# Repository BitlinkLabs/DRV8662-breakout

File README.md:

# DRV8662-breakout

<p align="center">
  
&nbsp; &nbsp; &nbsp; &nbsp;
  
&nbsp; &nbsp; &nbsp; &nbsp;
  
</p>

### What is it?
This is a ready-to-go development board with everything necessary to run piezo actuators.
It features a DRV8662 IC from Texas Instruments and all the additional circuitry for it to work as expected.

### How does it function?
The IC serves multiple purposes. First of all it is a boost-converter to generate up 200V from the 3.3-5V it takes as an input. Secondly it features an amplifier which takes a PWM Signal and drives the Output pins to the respective differential values according to the input.

At the output you can connect a piezo actuator for haptic feedback or valves & pumps.
The output voltage is an AC Waveform with an adjustable Peak-to-Peak voltage.

### What is special about it?
The Output voltage can be to 4 approximate values: 50Vpp, 100Vpp, 150Vpp, 200Vpp using a simple dip switch.

### How do I get started?
All you need to do is connect an PWM and GND pin of a microcontroller to the PWM+ Pin and GND pin of the development board respectively. This covers the “signal” part.
To power the dev board you can either use the USB mini jack (we recommend using a USB hub for this) or through the included VCC and GND Pins. 
Be sure to stick to an input voltage of 3.3V to 5V and be aware that the USB voltage will be present on the VCC pin.

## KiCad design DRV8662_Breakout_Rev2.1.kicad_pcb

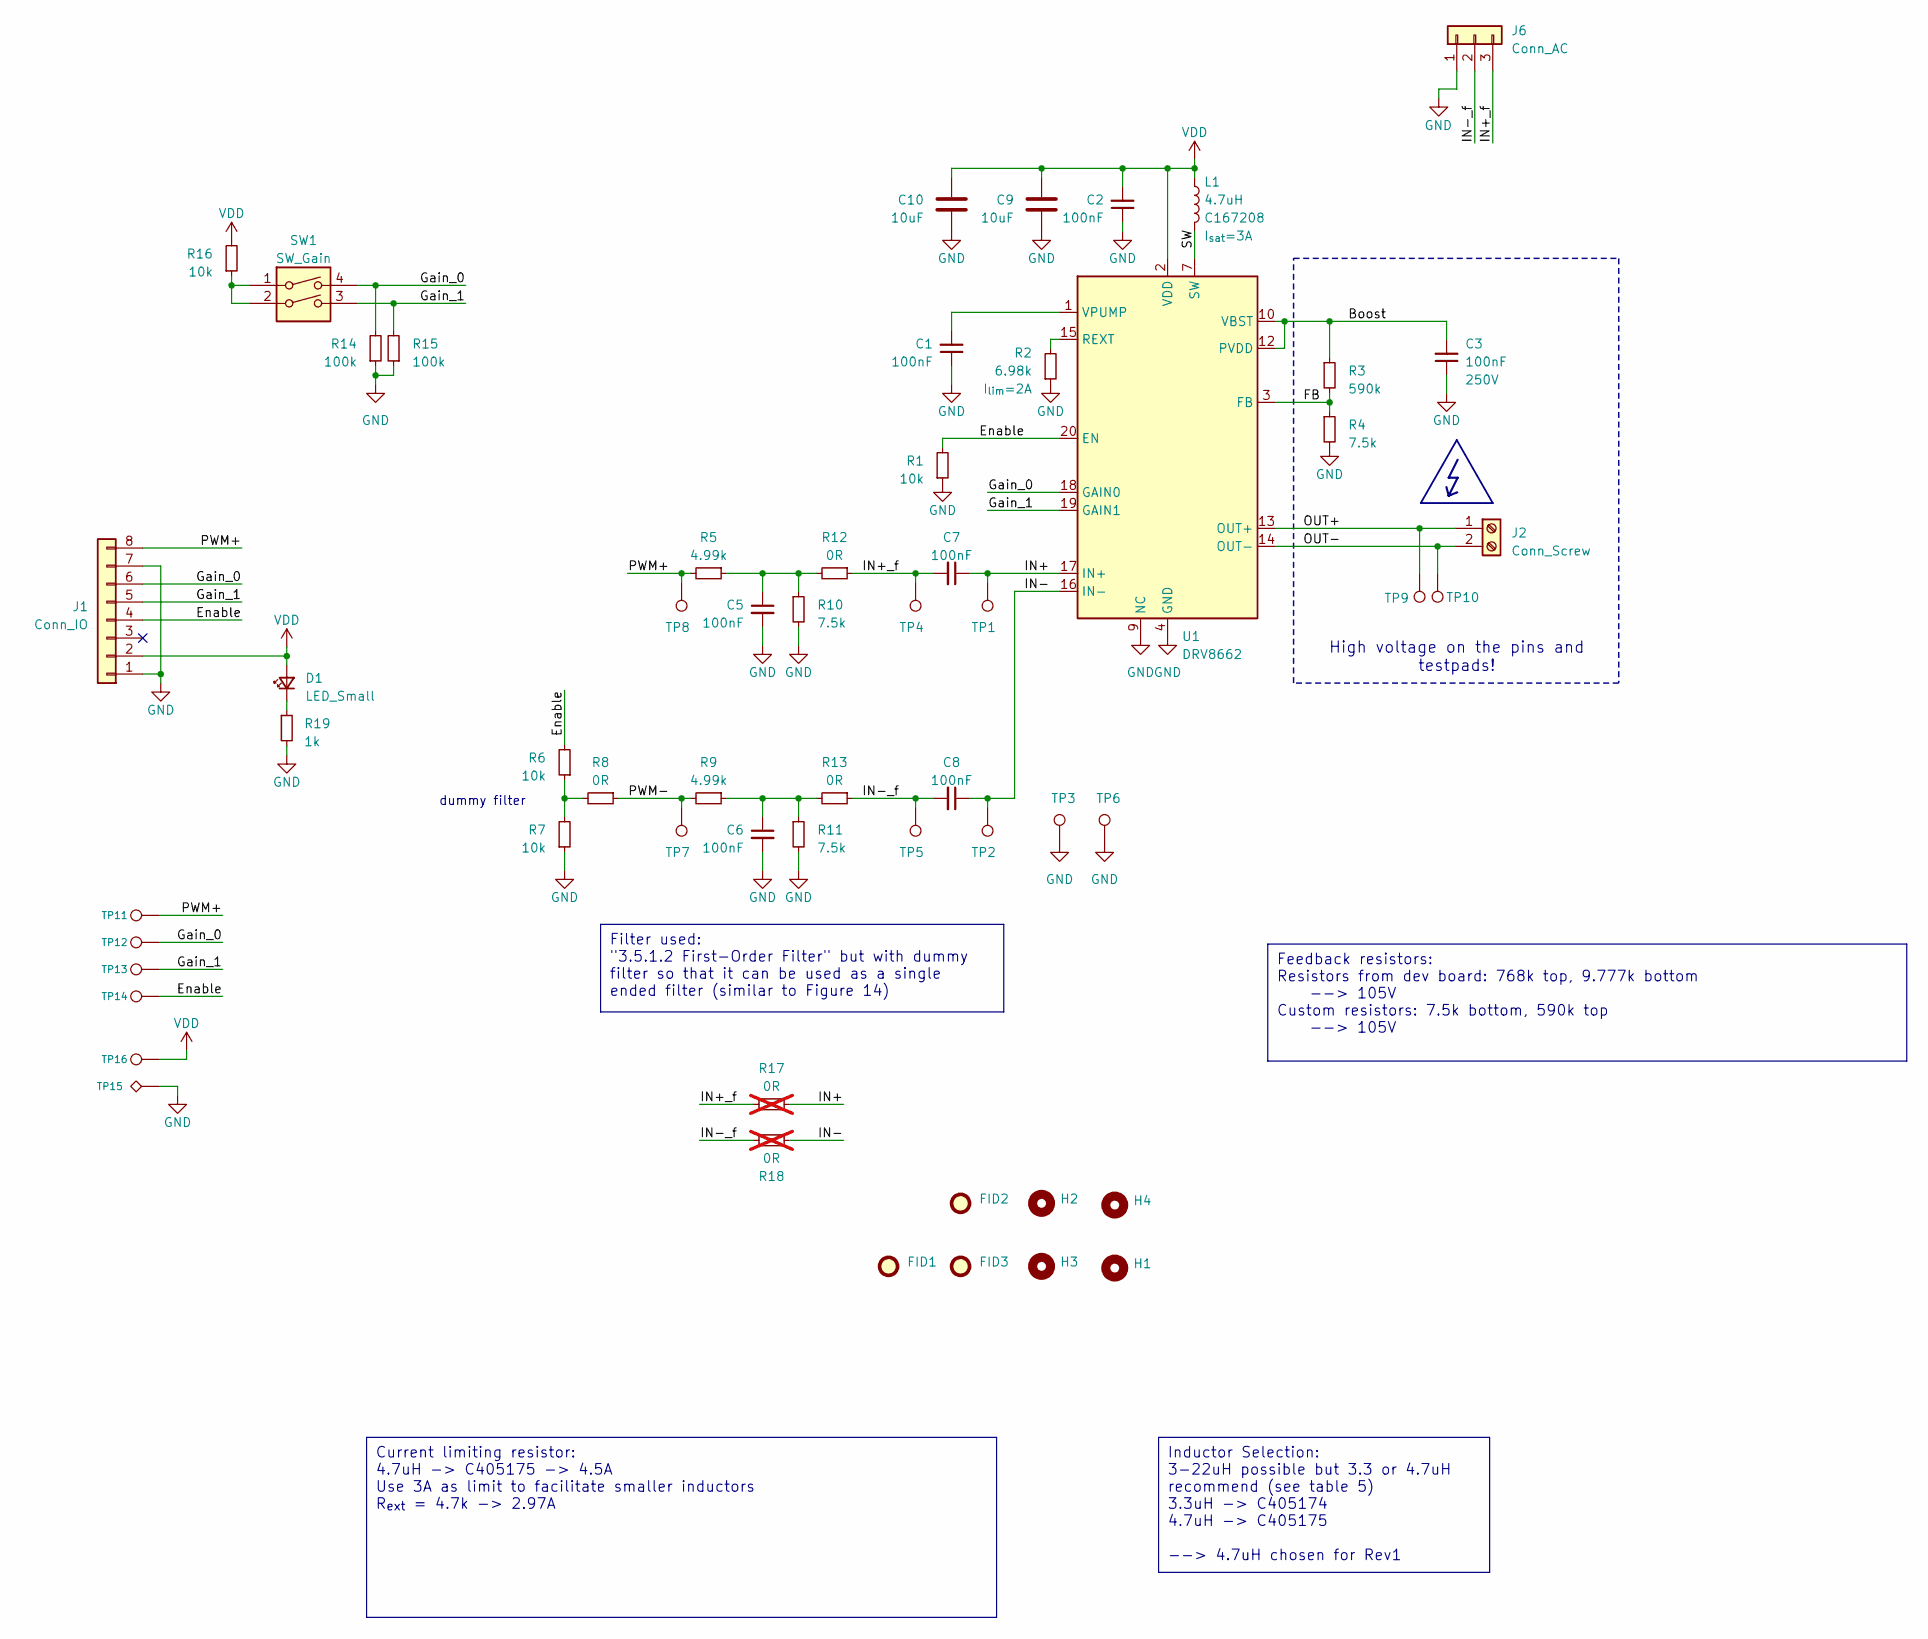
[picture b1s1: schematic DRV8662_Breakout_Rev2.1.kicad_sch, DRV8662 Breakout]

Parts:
C1, C2, C5, C6, C7, C8: 100nF; C_0603_1608Metric; PartNumber C14663; LCSC Part # C14663
C3: 100nF; C_1206_3216Metric; Voltage 250V; PartNumber C346235; LCSC Part # C346235
C9, C10: 10uF; C_1206_3216Metric; PartNumber C13585; LCSC Part # C13585
D1: LED_Small; LED_0805_2012Metric; LCSC Part # C84256
FID1, FID2, FID3: Fiducial; Fiducial_standart
H1, H2, H3, H4: MountingHole; MountingHole_3.2mm_M3_ISO7380_Pad_TopBottom
J1: Conn_IO; PinHeader_1x08_P2.54mm_Horizontal_withSmdPads
J2: Conn_Screw; DB128L-5.08-2P; PartNumber C430603; LCSC Part # C430603
J6: Conn_AC; PinHeader_1x03_P2.54mm_Vertical
L1: 4.7uH; Inductor_FXL0420-4R7-M; PartNumber C167208; LCSC Part # C167208
R1, R6, R7, R16: 10k; R_0603_1608Metric; PartNumber C25804; LCSC Part # C25804
R2: 6.98k; R_0603_1608Metric_Pad0.98x0.95mm_HandSolder; PartNumber C862806; LCSC Part # C862806
R3: 590k; R_0603_1608Metric_Pad0.98x0.95mm_HandSolder; PartNumber C185318; LCSC Part # C185318
R4, R10, R11: 7.5k; R_0603_1608Metric; PartNumber C23234; LCSC Part # C23234
R5, R9: 4.99k; R_0603_1608Metric; PartNumber C23046; LCSC Part # C23046
R8, R12, R13: 0R; Jumper_Small-2_bridged; PartNumber C21189
R14, R15: 100k; R_0603_1608Metric; LCSC Part # C25803
R17, R18: 0R; Jumper_Small-2_open; PartNumber C21189; not fitted
R19: 1k; R_0603_1608Metric; LCSC Part # C21190
SW1: SW_Gain; SW_DIP_x02_P2.54_W5.08_C6709488; PartNumber C6709488; LCSC Part # C6709488
TP1, TP2, TP4, TP5, TP7, TP8: TestPoint; TestPoint_Pad_D1.0mm_NoSilk
TP3, TP6: TestPoint; TestPoint_Pad_1.0x1.0mm
TP9, TP10, TP11, TP12, TP13, TP14, TP16: TestPoint; TestPoint_Pad_D1.5mm_NoSilk
TP15: TestPoint_Alt; TestPoint_Pad_1.5x1.5mm
U1: DRV8662; Texas_S-PVQFN-N20_EP2.7x2.7mm_ThermalVias; PartNumber C181554; LCSC Part # C181554

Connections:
/Boost: C3.2, R3.1, U1.10 (VBST), U1.11 (VBST), U1.12 (PVDD)
/Enable: J1.4, R1.2, R6.2, TP14.1, U1.20 (EN)
/FB: R3.2, R4.1, U1.3 (FB)
/Gain_0: J1.6, R14.2, SW1.4, TP12.1, U1.18 (GAIN0)
/Gain_1: J1.5, R15.2, SW1.3, TP13.1, U1.19 (GAIN1)
/IN+: C7.1, R17.1, TP1.1, U1.17 (IN+)
/IN+_f: C7.2, J6.3, R12.1, R17.2, TP4.1
/IN-: C8.1, R18.1, TP2.1, U1.16 (IN-)
/IN-_f: C8.2, J6.2, R13.1, R18.2, TP5.1
/OUT+: J2.1, TP9.1, U1.13 (OUT+)
/OUT-: J2.2, TP10.1, U1.14 (OUT-)
/PWM+: J1.8, R5.2, TP8.1, TP11.1
/PWM-: R8.1, R9.2, TP7.1
/SW: L1.2, U1.7 (SW), U1.8 (SW)
GND: C1.1, C2.1, C3.1, C5.2, C6.2, C9.2, C10.2, J1.1, J1.7, J6.1, R1.1, R2.1, R4.2, R7.1, R10.2, R11.2, R14.1, R15.1, R19.2, TP3.1, TP6.1, TP15.1, U1.4 (GND), U1.5 (GND), U1.6 (GND), U1.9 (NC), U1.21 (GND)
unnamed: C5.1, R5.1, R10.1, R12.2
unnamed: C6.1, R9.1, R11.1, R13.2
unnamed: D1.1 (K), R19.1
unnamed: R6.1, R7.2, R8.2
unnamed: R16.1, SW1.1, SW1.2
unnamed: R2.2, U1.15 (REXT)
unnamed: C1.2, U1.1 (VPUMP)
VDD: C2.2, C9.1, C10.1, D1.2 (A), J1.2, L1.1, R16.2, TP16.1, U1.2 (VDD)

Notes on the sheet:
Current limiting resistor: 4.7uH -> C405175 -> 4.5A Use 3A as limit to facilitate smaller inductors R_{ext} = 4.7k -> 2.97A
Filter used: "3.5.1.2 First-Order Filter" but with dummy filter so that it can be used as a single ended filter (similar to Figure 14)
Feedback resistors: Resistors from dev board: 768k top, 9.777k bottom --> 105V Custom resistors: 7.5k bottom, 590k top --> 105V
High voltage on the pins and testpads!
Inductor Selection: 3-22uH possible but 3.3 or 4.7uH recommend (see table 5) 3.3uH -> C405174 4.7uH -> C405175 --> 4.7uH chosen for Rev1
dummy filter

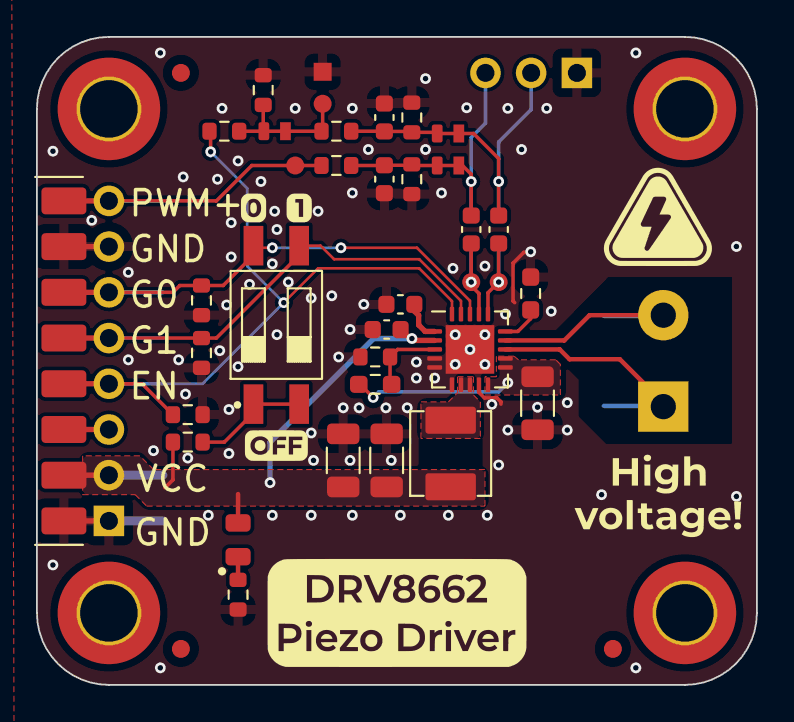
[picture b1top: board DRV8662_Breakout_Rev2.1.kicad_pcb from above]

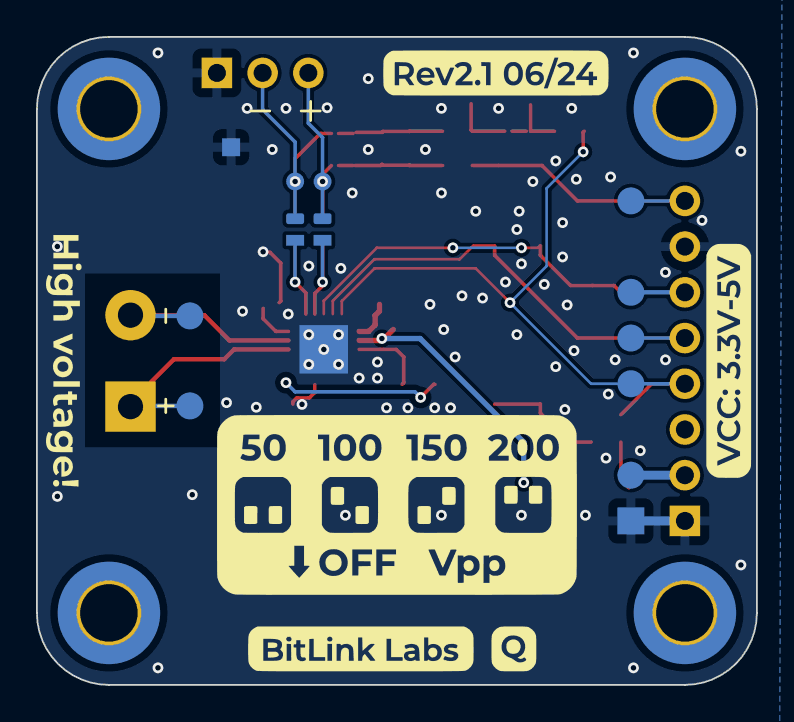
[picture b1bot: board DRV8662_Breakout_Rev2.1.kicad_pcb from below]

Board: 2 copper layers, 40.0 x 36.0 mm, 58 parts (13 on the bottom side), 23 nets.

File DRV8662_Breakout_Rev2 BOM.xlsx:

DRV 8662 Breakout Rev2 |  |  |  |  |  |  |  | (Stand 27.03.24)
Ref | Description | Qnty | Value | Cmp name | Footprint | VoltageRating | ManuNumber | LCSC Part Number | Stock | Link | Datasheet
C1, C2, C5, C6, C7, C8, |  | 6 | 100nF | C_Small | Capacitor_SMD:C_0603_1608Metric |  |  | C14663 | At home | https://jlcpcb.com/partdetail/Yageo-CC0603KRX7R9BB104/C14663 | ~
C3, | 250V Boost cap. | 1 | 100nF | C_Small | Capacitor_SMD:C_1206_3216Metric |  |  | C346235 |  | https://www.lcsc.com/product-detail/Multilayer-Ceramic-Capac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 | ~
C9, C10, |  | 2 | 10uF | C | Capacitor_SMD:C_1206_3216Metric |  |  | C13585 |  | https://www.lcsc.com/product-detail/Multilayer-Ceramic-Capac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 | ~
D1, |  | 1 | LED_Small | LED_Small | LED_SMD:LED_0805_2012Metric |  |  |  | At home |  | ~
J1, |  | 1 | Conn_IO | Conn_01x08 | MAINTECH_Connectors:PinHeader_1x08_P2.54mm_Horizontal_withSmdPads |  |  |  | At home |  | ~
J2, | Orange screw terminal | 1 | Conn_Screw | Screw_Terminal_01x02 | MAINTECH_Connectors:DB128L-5.08-2P |  |  | C430603 |  | https://www.lcsc.com/product-detail/Screw-terminal_DORABO-DB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 | ~
L1, | Inductor | 1 | 4.7uH | L | MAINTECH_Passives:Inductor_FXL0420-4R7-M |  | FXL0420-4R7-M | C167208 |  | https://www.lcsc.com/product-detail/Power-Inductors_cjiang-C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 | ~
R1, R6, R7, R16, |  | 4 | 10k | R_Small | Resistor_SMD:R_0603_1608Metric |  |  | C25804 | At home | https://jlcpcb.com/partdetail/26547-0603WAF1002T5E/C25804 | ~
R14, R15, |  | 2 | 100k | R_Small | Resistor_SMD:R_0603_1608Metric
R2, |  | 1 | 6.98k | R_Small | Resistor_SMD:R_0603_1608Metric_Pad0.98x0.95mm_HandSolder |  |  | C862806 |  | https://www.lcsc.com/product-detail/Chip-Resistor-Surface-Mo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 | ~
R3, |  | 1 | 590k | R_Small | Resistor_SMD:R_0603_1608Metric_Pad0.98x0.95mm_HandSolder |  |  | C185318 |  | https://www.lcsc.com/product-detail/Chip-Resistor-Surface-Mo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 | ~
R4, |  | 1 | 7.5k | R_Small | Resistor_SMD:R_0603_1608Metric_Pad0.98x0.95mm_HandSolder |  |  | C23234 |  | https://www.lcsc.com/product-detail/Chip-Resistor-Surface-Mo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 | ~
R5, R9, |  | 2 | 4.99k | R_Small | Resistor_SMD:R_0603_1608Metric |  |  | C23046 |  | https://www.lcsc.com/product-detail/Chip-Resistor-Surface-Mo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 | ~
R8, R12, R13, |  | 3 | 0R | R_Small | Resistor_SMD:R_0603_1608Metric_Pad0.98x0.95mm_HandSolder |  |  | C21189 |  | https://www.lcsc.com/product-detail/Chip-Resistor-Surface-Mo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 | ~
R10, R11, | FB & Filter Resistor | 2 | 7.5k | R_Small | Resistor_SMD:R_0603_1608Metric |  |  | C23234 |  | https://www.lcsc.com/product-detail/Chip-Resistor-Surface-Mo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 | ~
R19, |  | 1 | 1k | R_Small | Resistor_SMD:R_0603_1608Metric |  |  |  | At home |  | ~
SW1, | Dip switch | 1 | SW_Gain | SW_DIP_x02 | MAINTECH_mechanical:SW_DIP_x02_P2.54_W5.08_C6709488 |  | 2.54-2P TPPT | C6709488 |  | https://www.lcsc.com/product-detail/DIP-Switches_SHOU-HAN-2-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 | ~
U1, | DRB8662 IC | 1 | DRV8662 | DRV8662 | Package_DFN_QFN:Texas_S-PVQFN-N20_EP2.7x2.7mm_ThermalVias |  |  | C181554 |  | https://www.lcsc.com/product-detail/Motor-Driver-ICs_Texas-I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 | http://www.ti.com/lit/ds/symlink/drv8662.pdf

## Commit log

2024-01-25 Added Schematic PDF
2024-01-25 Delected PDF
2024-01-25 Added PDF Schematic
2024-01-25 .gitignore
2024-02-10 Add Arduino example
2024-03-27 Added Rev2 design data and moved Rev1 Schematic to /Rev1
2024-07-01 Added Rev2.1 and moved Rev2 into separate folder. Added new Rev2.1 Images.
2024-07-01 Fixed image aspect ratio.
2024-07-17 update link in readme
2024-07-17 add example code for rp2040
